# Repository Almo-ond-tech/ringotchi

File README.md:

# ringotchi

# Description
A tamagotchi pet with an apple shape. The usb port plugs into the top of the apple to form the stem. The sprite for the pet is a cat with glasses to match the case. And it has a pet worm because it lives in an apple. I made this following the tutorial for hackclub fallout: [https://fallout.hackclub.com/docs/guided-projects/tamagotchi].
I like retro toys and I'm glad I get to make my own custom tamagotchi that I can personalise to do stuff. I'm thinking of adding extra stuff like a death screen and mini game but I'll just wait to build it in real life first. I also used this github as reference to program the jingles: https://github.com/FeFaxy/arduino_buzzer/blob/main/Twinkle_Twinkle_Little_Star.ino

<h2> Functions</h2>

</ul>
<h3> DISPLAY </h3>
<ul>
  <li> On the display there are three labels on the left aranged vertically and one label on the right. 
  <p> These labales correspond to the three switches on the left and the rotary encoder on the right. From top to down it goes: "[Feed]", "[Play]" and "[Sleep]". Then on the right: "[Bath]".  </p> </li>
  <li> At the bottom of the display there are the pet's current stats in long rectangular bars, which fill up in percentage according to the current value of said stat. It goes from top to bottom in the order: "HUN" (HUNGER), "HAP" (HAPPINESS), "ENG" (ENERGY), "HYG" (HYGIENE). </li>
  <li> The screen also features an age variable which keeps track of how many minutes your pet has been alive. </li>
  </ul>
  
<h3> BUTTONS </h3>
<ul>
  <li>The first button triggers the feed screen. The leds blinks and the buzzer rings in morse code to form the message: "EAT"
    <p>On this screen pressing the same button increases the hunger and energy stat and makes the pet more full. When the hunger stat reaches 100 the tamagotchi plays a little jingle</p> 
  </li>
  
  <li> The second button triggers the play screen. The leds blinks and the buzzer rings in morse code to form the message: "YAY"
     <p>On this screen pressing the same button increases the happiness stat but decreases the energy stat making the pet feel more tired. When the happiness reaches 100 the tamagotchi plays a little jingle</p> </li>

  <li> The third button triggers the sleep screen. The leds blinks and the buzzer rings in morse code to form the message: "ZZZ"
  <p>On this screen pressing the same button increases the energy stat and makes the pet feel more energetic. When the energy reaches 100 the tamagotchi plays a little jingle </p>
  </li>
  
  <li> The fourth button triggers the bath screen. The leds blinks and the buzzer rings in morse code to form the message: "EWW" 
    <p> On this screen you need to turn the rotary encoder a certain amount of time before the hygiene and energy stat increases. The screen displays how many turn are left to increment the stats by the set value. Each turn is equal to 5 rotations. Rotating the encoder a combined amount of 15 time to either the left and or right increases these stats imitaiting a scrubbing motion. Pressing the rotary encoder again returns back to the main screen. When the hygiene stat reaches 100 the tamagotchi plays a little jingle</p> </li>  
</ul>

<h3> MODES </h3>
<ul>
  <li> If the energy stat is below 40 the pet is tired and displays this image: <br>
    
 </li>
  <li> If the hygiene is below 30 the pet is dirty and displays this image: <br>
    
 </li>
  <li> If the hunger and happiness stats are below 30 the pet is sad and displays this image: <br> 
    
</li>
  <li> If the energy and happiness stats are above 60 the pet is happy and displays this image: <br> 
    
</li>  
<li>
  If the above conditions for the modes aren't met the pet has a neutral expression:  <br>
  
</li>

### Disclaimer
Since I haven't build it in real life yet there are bound to be inaccuracies in the code or hardware. However I've tried my best to minimize those as much as possible. This image is thus just a vague rendition of what the screen could theoretically look like with the current code. <br>

# Firmware setup
Make sure you have the neccesary libraries downloaded in Arduino ide. Select the board and configure the pins to match your pin numbers. At this step you can also customize the ringotchi. <br>
 <br>
You can change the tunes that play by changing the notes in the (something_)jingle functions. <br>
 <br>
And also change the pattern of the morse code to be other messages in the morse(_something) variable at the top. <br>
 <br>
Furthermore you can even customize your sprite by drawing it in [https://draw-to-bit.vercel.app/], copying the progmem(c) and replacing it in the code for PROGMEM pet(something). <br> 
 <br>

However make sure it is a 32 x 32 bit sprite as those are the dimensions used in this code. After customizing to your hearts desire upload the code to the Xiao ESPC3 and put together the casing.

# Casing
<a href='https://cad.onshape.com/documents/550f27ac1857586e625d99ee/w/67f007c674e2b675580248ba/e/c8e1a93a35cedfa3546ef407?renderMode=0&uiState=6a361b78c68ee69fbb8f3a63'>
Onshape link </a> <br> Or copy paste in browser: [https://cad.onshape.com/documents/550f27ac1857586e625d99ee/w/67f007c674e2b675580248ba/e/c8e1a93a35cedfa3546ef407?renderMode=0&uiState=6a361b78c68ee69fbb8f3a63] <br>

<h4>Step 1 :</h4> Building the casing is pretty straight forward.You print out the top and bottom case and gather the nessecary screws.
<h4> Step 1.5 (Optional): </h4> Paint and coat the case in your preffered colors. I recommend colors similar to the 3d model.
<h4> Step 2: </h4> Place the LiPo battery in the bottom compartment of the bottom case and connect it to the headers on the pcb.

<h4> Step 3:</h4> Screw the pcb in place using two M3 screws on either sides of the pcb.

<h4>Step 4:</h4> Attach the top case by screwing it in place using 6 M3 screws.

Your Ringotchi is now fully assembled!

# PCB

<h2> Schematics</h2>

<h2> 3d Model PCB</h2>

<h2>PCB Routing </h2>

# BOM (Bill of Materials)
[Ringotchi BOM - Sheet1.csv](https://github.com/user-attachments/files/29273973/Ringotchi.BOM.-.Sheet1.csv)

| Item                                                                                               | Description                                 | Quantity | Unit Price ($) | Total Price($) | URL                                                                                                                                                                                                                                                                                                                                                                                                                                                                                                                                                                                                                                                                                                                                                                                                                                                                                                                                        | Running Total With Tax ($) |
|----------------------------------------------------------------------------------------------------|---------------------------------------------|----------|----------------|----------------|--------------------------------------------------------------------------------------------------------------------------------------------------------------------------------------------------------------------------------------------------------------------------------------------------------------------------------------------------------------------------------------------------------------------------------------------------------------------------------------------------------------------------------------------------------------------------------------------------------------------------------------------------------------------------------------------------------------------------------------------------------------------------------------------------------------------------------------------------------------------------------------------------------------------------------------------|----------------------------|
| M3 screws (50 pcs)                                                                                 | 3mm diameter counter sunk screws 8mm (6pcs) | 1        | 0.1296         | 6.48           | https://nl.aliexpress.com/item/1005008709978631.html?spm=a2g0o.detail.pcDetailTopMoreOtherSeller.2.454fftMBftMBpy&gps-id=pcDetailTopMoreOtherSeller&scm=1007.40050.354490.0&scm_id=1007.40050.354490.0&scm-url=1007.40050.354490.0&pvid=83f03170-c03f-4f9e-a1b3-7860960ec42c&_t=gps-id%3ApcDetailTopMoreOtherSeller%2Cscm-url%3A1007.40050.354490.0%2Cpvid%3A83f03170-c03f-4f9e-a1b3-7860960ec42c%2Ctpp_buckets%3A668%232846%238114%231999&pdp_ext_f=%7B%22order%22%3A%2211679%22%2C%22eval%22%3A%221%22%2C%22sceneId%22%3A%2230050%22%2C%22fromPage%22%3A%22recommend%22%7D&pdp_npi=6%40dis%21EUR%211.96%211.80%21%21%2114.93%2113.73%21%400b884b5817817984658936804e0fbf%2112000046342342830%21rec%21NL%213328622363%21XZ%211%210%21n_tag%3A-29919%3Bd%3A9b918edc%3Bm03_new_user%3A-29895%3BpisId%3A5000000209393528&utparam-url=scene%3ApcDetailTopMoreOtherSeller%7Cquery_from%3A%7Cx_object_id%3A1005008709978631%7C_p_origin_prod%3A | 6.48                       |
| Lithium Polymer Battery 3.7 V 500 mAh 403048 Lipo Rechargeable Battery with Wired JST Connector    | LiPo Battery                                | 1        | 11.6           | 11.6           | https://www.amazon.nl/gp/product/B095W6742D/ref=ox_sc_act_title_1?smid=ASLRAS85RTYN3&th=1                                                                                                                                                                                                                                                                                                                                                                                                                                                                                                                                                                                                                                                                                                                                                                                                                                                  | 11.6                       |
| 12*9.5mm Mini Active Piezo Buzzers (10 pcs)                                                        | 12x9.5 Buzzer 1pc                           | 1        | 0.694          | 6.94           | https://nl.aliexpress.com/item/1005010321957502.html?gatewayAdapt=usa2nld4itemAdapt                                                                                                                                                                                                                                                                                                                                                                                                                                                                                                                                                                                                                                                                                                                                                                                                                                                        | 1                          |
| ESP32 C3 Development Board for Arduino Seeed Studio XIAO ESP32C3                                   | MCU                                         | 1        | 6.26           | 6.26           | https://nl.aliexpress.com/item/1005006979844970.html?spm=a2g0o.productlist.main.1.37f9760dY6UkfV&algo_pvid=e796eff8-5341-4eeb-94a3-04cde44d927c&algo_exp_id=e796eff8-5341-4eeb-94a3-04cde44d927c-0&pdp_ext_f=%7B%22order%22%3A%22506%22%2C%22spu_best_type%22%3A%22price%22%2C%22eval%22%3A%221%22%2C%22fromPage%22%3A%22search%22%7D&pdp_npi=6%40dis%21EUR%2111.93%215.49%21%21%2190.17%2141.49%21%40211b6c1717822614569675506eeb93%2112000051688055643%21sea%21NL%210%21ABX%211%210%21n_tag%3A-29910%3Bd%3A9b918edc%3Bm03_new_user%3A-29895&curPageLogUid=BNs0zElQh3h5&utparam-url=scene%3Asearch%7Cquery_from%3A%7Cx_object_id%3A1005006979844970%7C_p_origin_prod%3A                                                                                                                                                                                                                                                                   | 6.26                       |
| 0.96 inch OLED display module SSD1306 I2C SPI serial 128X64 LCD 4-pin white (Pin Headers soldered) | OLED Display                                | 1        | 2.5            | 2.5            | https://nl.aliexpress.com/item/1005006996785298.html?spm=a2g0o.productlist.main.7.3fa6sXSnsXSn6B&algo_pvid=0320fd94-73fb-46c3-b134-a735887beb62&algo_exp_id=0320fd94-73fb-46c3-b134-a735887beb62-6&pdp_ext_f=%7B%22order%22%3A%2233299%22%2C%22eval%22%3A%221%22%2C%22orig_sl_item_id%22%3A%221005006996785298%22%2C%22orig_item_id%22%3A%221005007389730469%22%2C%22fromPage%22%3A%22search%22%7D&pdp_npi=6%40dis%21EUR%214.40%210.89%21%21%2133.25%216.73%21%40211b441e17822617235672929e65bb%2112000038989536071%21sea%21NL%210%21ABX%211%210%21n_tag%3A-29910%3Bd%3A9b918edc%3Bm03_new_user%3A-29895%3BpisId%3A5000000205243325&curPageLogUid=Dw1SKvcomtXI&utparam-url=scene%3Asearch%7Cquery_from%3A%7Cx_object_id%3A1005006996785298%7C_p_origin_prod%3A1005007389730469                                                                                                                                                             | 2.5                        |
| 5 pcs Encoder Switch EC11 With Push Button Switch 5-pin Plug-in 15mm Half Plump Shaft              | Rotary Encoder with push button 1pc         | 1        | 0.648          | 3.24           | https://nl.aliexpress.com/item/1005009120433387.html?spm=a2g0o.detail.pcDetailTopMoreOtherSeller.13.2f7feUDoeUDoei&gps-id=pcDetailTopMoreOtherSeller&scm=1007.40050.354490.0&scm_id=1007.40050.354490.0&scm-url=1007.40050.354490.0&pvid=6460b935-0420-4cc0-84cc-4b231cf40f24&_t=gps-id%3ApcDetailTopMoreOtherSeller%2Cscm-url%3A1007.40050.354490.0%2Cpvid%3A6460b935-0420-4cc0-84cc-4b231cf40f24%2Ctpp_buckets%3A668%232846%238111%231996&pdp_ext_f=%7B%22order%22%3A%22471%22%2C%22eval%22%3A%221%22%2C%22sceneId%22%3A%2230050%22%2C%22fromPage%22%3A%22recommend%22%7D&pdp_npi=6%40dis%21EUR%213.56%212.85%21%21%213.97%213.18%21%400b88ab7917822626711124499e10dc%2112000047989804997%21rec%21NL%21%21ABXZ%211%210%21n_tag%3A-29910%3Bd%3A9b918edc%3Bm03_new_user%3A-29895&utparam-url=scene%3ApcDetailTopMoreOtherSeller%7Cquery_from%3A%7Cx_object_id%3A1005009120433387%7C_p_origin_prod%3A                                       | 3.24                       |
| Tactile Switch 6x6x10mm Center pin 2 pins (20 pcs)                                                 | 6mm Tactile switches 3pcs                   | 1        | 0.312          | 6.24           | https://nl.aliexpress.com/item/1005006120482626.html?spm=a2g0o.productlist.main.1.40354ccbylfe9E&algo_pvid=6e561830-6e62-4b52-ad51-589a1727a57a&algo_exp_id=6e561830-6e62-4b52-ad51-589a1727a57a-0&pdp_ext_f=%7B%22order%22%3A%22475%22%2C%22eval%22%3A%221%22%2C%22fromPage%22%3A%22search%22%7D&pdp_npi=6%40dis%21EUR%215.41%213.62%21%21%2140.90%2127.37%21%402103864c17822638743823953ee021%2112000035862032475%21sea%21NL%210%21ABX%211%210%21n_tag%3A-29910%3Bd%3A9b918edc%3Bm03_new_user%3A-29895%3BpisId%3A5000000205243325&curPageLogUid=iZrToCtnBZvV&utparam-url=scene%3Asearch%7Cquery_from%3A%7Cx_object_id%3A1005006120482626%7C_p_origin_prod%3A                                                                                                                                                                                                                                                                             | 6.24                       |
| 50 Pieces 2.54mm Single Row Pin Header Connector Strip 2Pin                                        | 2pin Pin Headers                            | 1        | 0.107          | 5.35           | https://nl.aliexpress.com/item/4000988113226.html?spm=a2g0o.cart.0.0.53c261d7OkfEao&mp=1&pdp_npi=6%40dis%21EUR%21EUR+1.79%21EUR+1.79%21%21EUR+1.79%21%21%21%402161390417815650514934912e10d2%2110000013202368857%21ct%21NL%213328622363%21%211%210%21&gatewayAdapt=glo2nld                                                                                                                                                                                                                                                                                                                                                                                                                                                                                                                                                                                                                                                                 | 5.35                       |
| 20 pieces metal film resistor 470K ohm                                                             | 470k ohm resistor                           | 1        | 0.4595         | 9.19           | https://nl.aliexpress.com/item/1005011814571889.html?spm=a2g0o.productlist.main.3.1b7c6511xsp3Yq&algo_pvid=1d3a1db1-713d-4efb-9de3-b824852553d3&algo_exp_id=1d3a1db1-713d-4efb-9de3-b824852553d3-2&pdp_ext_f=%7B%22order%22%3A%22123%22%2C%22eval%22%3A%221%22%2C%22fromPage%22%3A%22search%22%7D&pdp_npi=6%40dis%21EUR%2116.77%218.03%21%21%21126.77%2160.68%21%40211b61bb17822653509184226ea90a%2112000056662713535%21sea%21NL%213328622363%21X%211%210%21n_tag%3A-29919%3Bd%3A9b918edc%3Bm03_new_user%3A-29895%3BpisId%3A5000000209850550&curPageLogUid=ArSjgp03ZoD7&utparam-url=scene%3Asearch%7Cquery_from%3A%7Cx_object_id%3A1005011814571889%7C_p_origin_prod%3A                                                                                                                                                                                                                                                                    | 9.19                       |
| 100 pcs 3mm LED Diode RGB                                                                          | 2 LEDs                                      | 1        | 0.0106         | 1.06           | https://nl.aliexpress.com/item/1005007989424003.html?spm=a2g0o.productlist.main.4.7ca62085FxEFKQ&aem_p4p_detail=202606231847252829649531052840004049485&algo_pvid=fe6b06b1-495e-4a56-9680-0fddfabc552d&algo_exp_id=fe6b06b1-495e-4a56-9680-0fddfabc552d-3&pdp_ext_f=%7B%22order%22%3A%22551%22%2C%22eval%22%3A%221%22%2C%22fromPage%22%3A%22search%22%7D&pdp_npi=6%40dis%21EUR%210.99%210.88%21%21%211.11%210.99%21%402103894417822656452717554e1bfb%2112000043174317952%21sea%21NL%213328622363%21X%211%210%21n_tag%3A-29919%3Bd%3A9b918edc%3Bm03_new_user%3A-29895&curPageLogUid=Hn4y39cmrsXJ&utparam-url=scene%3Asearch%7Cquery_from%3A%7Cx_object_id%3A1005007989424003%7C_p_origin_prod%3A&search_p4p_id=202606231847252829649531052840004049485_1                                                                                                                                                                                    | 1.06                       |
| **TOTAL** | | | | **58.86** | | |

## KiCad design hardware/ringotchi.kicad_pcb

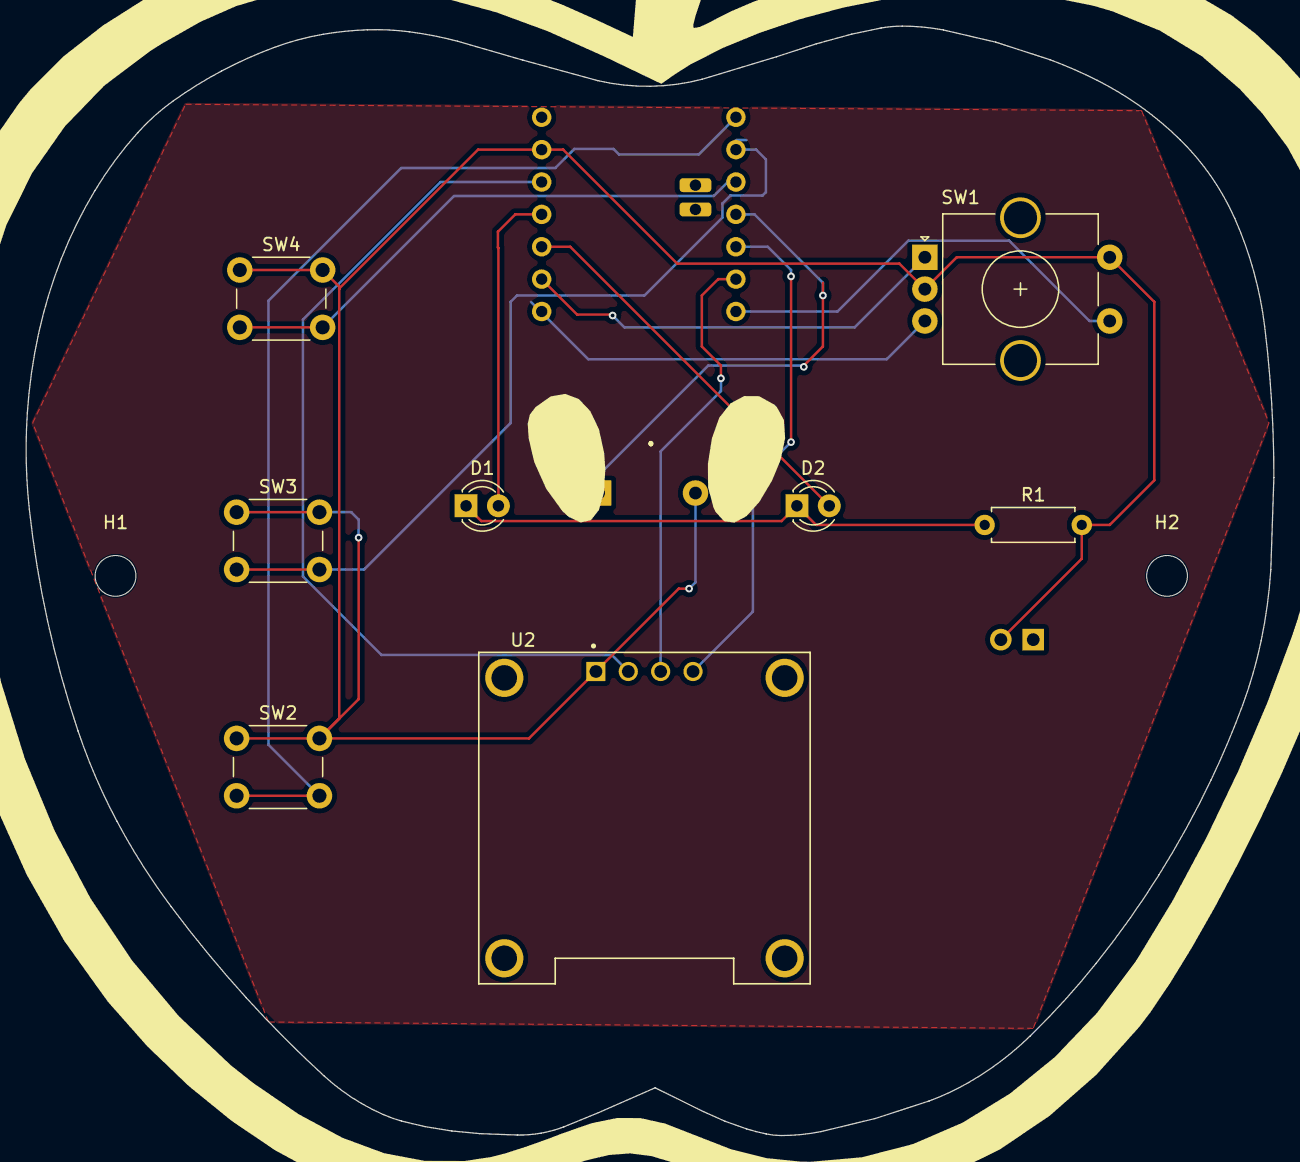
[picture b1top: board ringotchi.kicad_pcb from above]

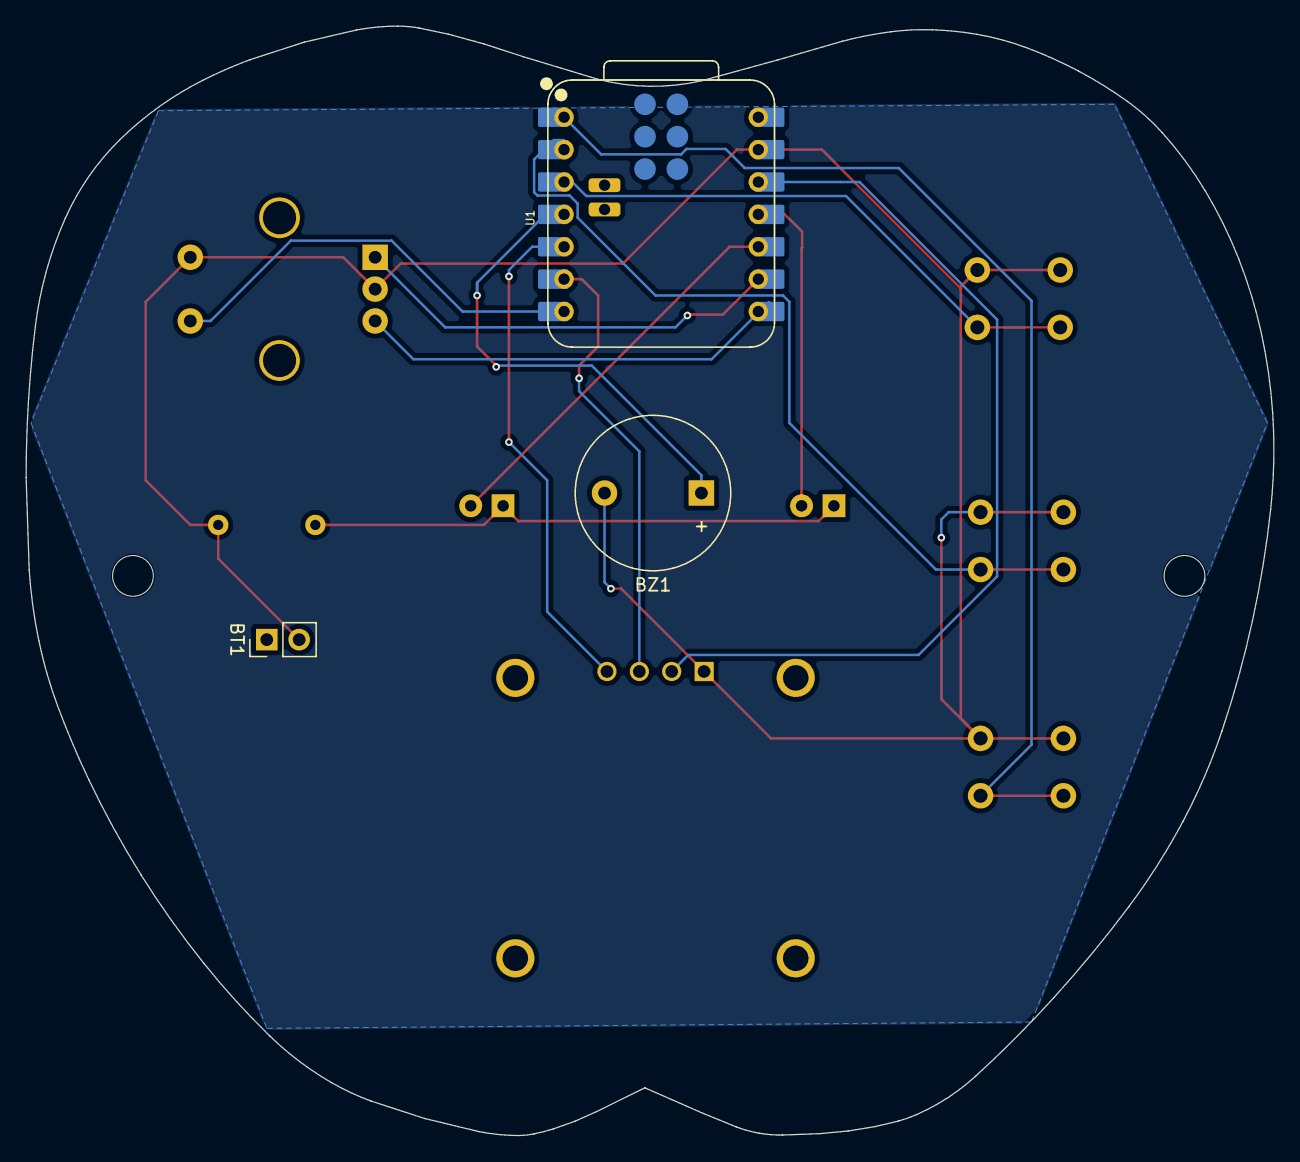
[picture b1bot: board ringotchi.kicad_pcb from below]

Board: 2 copper layers, 97.9 x 87.0 mm, 14 parts (3 on the bottom side), 14 nets.

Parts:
.: LOGO; apple_outline
BT1: Battery_Cell; PinHeader_1x02_P2.54mm_Vertical
BZ1: Buzzer; Buzzer_12x9.5RM7.6
D1, D2: LED; LED_D3.0mm
H1, H2: MountingHole; MountingHole_3.2mm_M3
R1: R; R_Axial_DIN0207_L6.3mm_D2.5mm_P7.62mm_Horizontal
SW1: RotaryEncoder_Switch_MP; RotaryEncoder_Alps_EC11E-Switch_Vertical_H20mm_CircularMoun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
SW2, SW3, SW4: SW_Push; SW_PUSH_6mm
U1: XIAO-ESP32-C3-SMD; XIAO-ESP32-C3-DIP-SMD
U2: DM-OLED096-636; MODULE_DM-OLED096-636

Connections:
+3V3: U1.12 (3V3), U2.2 (VCC_IN)
GND: BT1.2 (-), BZ1.2 (-), R1.2, SW1.C (GND), SW1.S2 (GND), SW2.1, SW3.1, SW4.1, U1.13 (GND), U2.1 (GND)
unnamed: BZ1.1 (+), U1.4 (GPIO5_A3_D3)
unnamed: D1.2 (A), U1.11 (GPIO10_D10_MOSI)
unnamed: D1.1 (K), D2.1 (K), R1.1
unnamed: D2.2 (A), U1.10 (GPIO9_D9_MISO)
unnamed: SW2.2, U1.1 (GPIO2_A0_D0)
unnamed: SW3.2, U1.2 (GPIO3_A1_D1)
unnamed: SW4.2, U1.3 (GPIO4_A2_D2)
unnamed: U1.5 (GPIO6_D4_SDA), U2.4 (SDA)
unnamed: U1.6 (GPIO7_D5_SCL), U2.3 (SCL)
unnamed: SW1.A, U1.9 (GPIO8_D8_SCK)
unnamed: SW1.B, U1.8 (GPIO20_D7_RX)
unnamed: SW1.S1, U1.7 (GPIO21_D6_TX)

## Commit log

2026-06-19 Rename ringotchi.kicad_pcb to hardware/ringotchi.kicad_pcb
2026-06-19 Rename ringotchi.kicad_pro to hardware/ringotchi.kicad_pro
2026-06-19 Rename ringotchi.kicad_sch to hardware/ringotchi.kicad_sch
2026-06-19 Rename ringotchi_pcb.png to hardware/ringotchi_pcb.png
2026-06-19 Rename ringotchi_pcb.png to ringotchi_pcb.png
2026-06-19 Rename schematic_ringotchi.png to docs/schematic_ringotchi.png
2026-06-19 Add images to README for schematic and PCB
    Added images to README for better visualization.
2026-06-19 Add 3D PCB images to README
    Added additional images of the PCB in 3D view.
2026-06-20 Add new images to README for ringotchi project
    Added additional images related to the ringotchi project.
2026-06-20 Add casing and PCB images to README
2026-06-20 Rename ringotchi_pcb.png to docs/ringotchi_pcb.png
2026-06-20 Rename 3dmodel.step to hardware/3dmodel.step
2026-06-20 Rename ringotchi_cad-bottom case.step to case_3d/ringotchi_cad-bottom case.step
2026-06-20 Rename ringotchi_cad-top case.step to case_3d/ringotchi_cad-top case.step
2026-06-24 Add new PCB 3D model file
2026-06-24 Rename Ringotchi BOM - Sheet1.csv to docs/Ringotchi BOM - Sheet1.csv
2026-06-24 Enhance README with project details and instructions
    Added detailed project description, functions, buttons, modes, and assembly instructions for the Ringotchi.
2026-06-24 Fix typo in README description
    Corrected a typo in the description of the tamagotchi pet.
